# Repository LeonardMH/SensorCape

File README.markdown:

# SensorCape

This is the project repository for the SensorCape for BeagleBone Black. The SensorCape is a highly capable add-on for the BeagleBone that adds the following functionality:

+ 3-axis gyroscope
+ 3-axis accelerometer
+ 3-axis magnetometer (compass)
+ Ambient light sensor
+ Ambient temperature sensor
+ Non-contact temperature sensor
+ Humidity sensor
+ Pressure sensor (Detects altitude changes)
+ 38 kHz IR sensor (Interfaces with common consumer electronics)
+ 4 push-buttons
+ 4 user-configurable LED's 

The repository hosts both the hardware files and the software library that is used to interact with the onboard sensors. Visit the [project page](http://michaelhleonard.com/projects/SensorCape) for further information and documentation.

## Checking out a specific folder

Since 2012 it has been possible to check out a specific folder in a git repository. This means that if you would like to develop or use the software but don't need the hardware files you don't have to clone them to your local computer. See [this stack overflow question](http://stackoverflow.com/questions/600079/is-there-any-way-to-clone-a-git-repositorys-sub-directory-only) for more info or [read this tutorial](http://jasonkarns.com/blog/subdirectory-checkouts-with-git-sparse-checkout/). You may also want to check out [the official documentation](http://schacon.github.io/git/git-read-tree.html#_sparse_checkout).

I would recommend just cloning the entire repository.

# Licenses

Hardware and software are released under the following licenses.

## Hardware

The SensorCape hardware is released under the open source ["SolderPad Hardware License"](http://solderpad.org/licenses/SHL-0.51/). The license disclaimer is below. This is an open source and fairly non-restrictive license.

Copyright SensorCape, Michael Leonard, Copyright and related rights are licensed under the Solderpad Hardware License, Version 0.51 (the “License”); you may not use this file except in compliance with the License. You may obtain a copy of the License at http://solderpad.org/licenses/SHL-0.51. Unless required by applicable law or agreed to in writing, software, hardware and materials distributed under this License is distributed on an “AS IS” BASIS, WITHOUT WARRANTIES OR CONDITIONS OF ANY KIND, either express or implied. See the License for the specific language governing permissions and limitations under the License.

## Software

The software library for the SensorCape (if it is ever finished) is released under the open source ["GNU Lesser General Public License v2.1"](http://www.gnu.org/licenses/lgpl-2.1.html). The license disclaimer is below. This is an open source and fairly non-restrictive license.

SensorCape for BeagleBone Black hardware interface library.
Copyright (C) 2014  Michael Leonard

This library is free software; you can redistribute it and/or
modify it under the terms of the GNU Lesser General Public
License as published by the Free Software Foundation; either
version 2.1 of the License, or any later version.

This library is distributed in the hope that it will be useful,
but WITHOUT ANY WARRANTY; without even the implied warranty of
MERCHANTABILITY or FITNESS FOR A PARTICULAR PURPOSE.  See the GNU
Lesser General Public License for more details.

You should have received a copy of the GNU Lesser General Public
License along with this library; if not, write to the Free Software
Foundation, Inc., 51 Franklin Street, Fifth Floor, Boston, MA  02110-1301  USA

You can contact me on GitHub as user [LeonardMH](http://github.com/LeonardMH).

# Contributors

Michael Leonard - [My Website](http://michaelhleonard.com/)

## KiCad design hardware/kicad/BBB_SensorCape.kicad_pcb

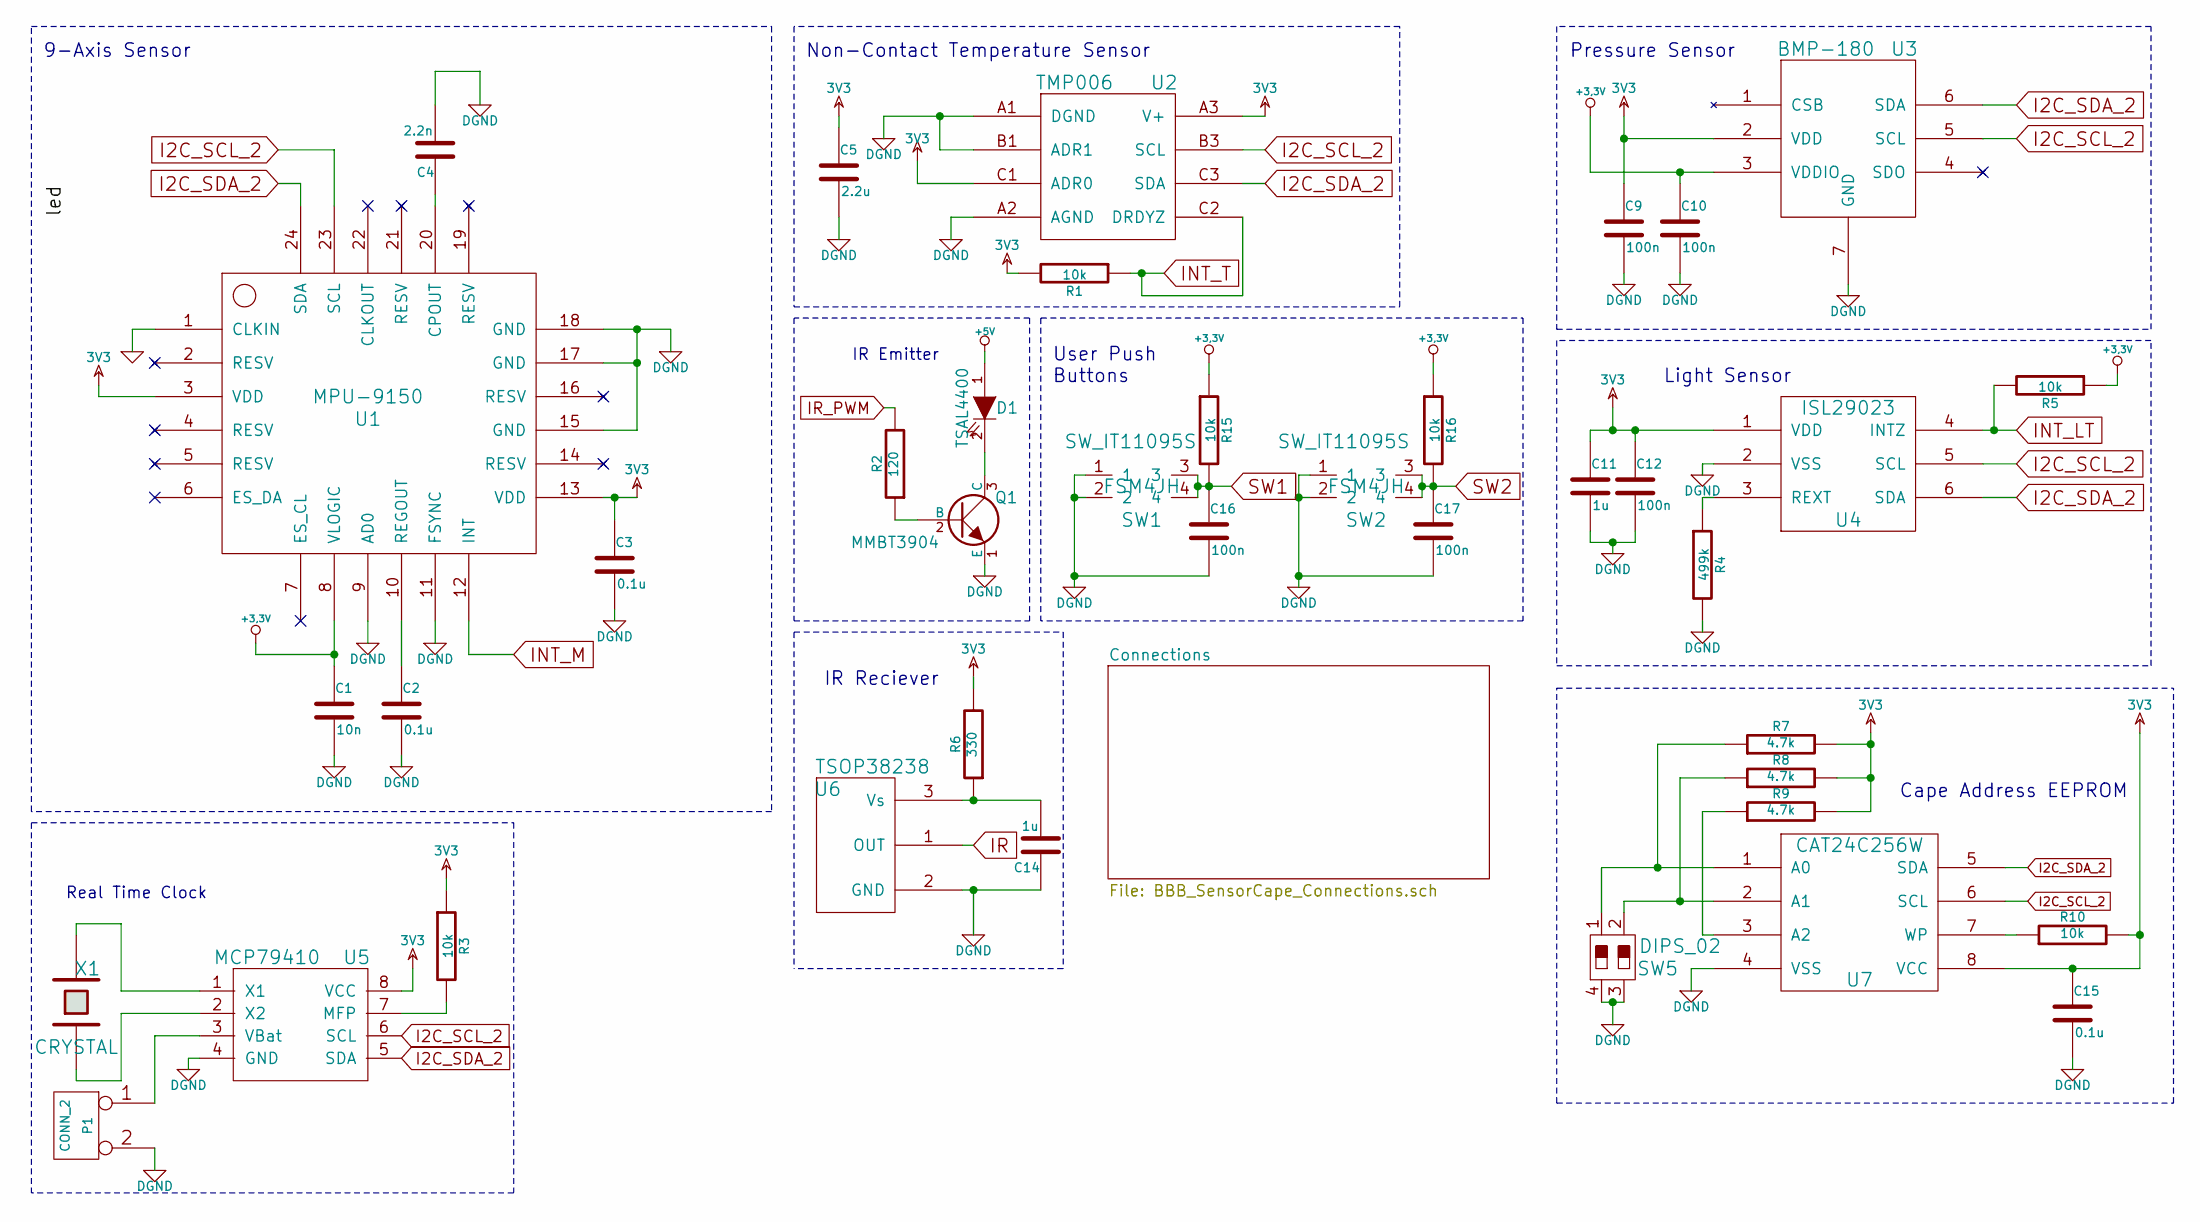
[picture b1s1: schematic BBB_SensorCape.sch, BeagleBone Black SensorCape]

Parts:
C1: 10n
C2, C3, C15: 0.1u
C4: 2.2n
C5: 2.2u
C9, C10, C12, C16, C17: 100n
C11, C14: 1u
D1: TSAL4400
P1: CONN_2
Q1: MMBT3904
R1, R3, R5, R10, R15, R16: 10k
R2: 120
R4: 499k
R6: 330
R7, R8, R9: 4.7k
SW1, SW2: SW_IT11095S; FSM4JH
SW5: DIPS_02
U1: MPU-9150
U2: TMP006
U3: BMP-180
U4: ISL29023
U5: MCP79410
U6: TSOP38238
U7: CAT24C256W
X1: CRYSTAL

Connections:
3V3: C3.1, C5.1, C9.1, C11.1, C12.1, C15.1, R1.2, R3.1, R6.2, R7.2, R8.2, R9.2, R10.2, U1.3 (VDD), U1.13 (VDD), U2.A3 (V+), U2.C1 (ADR0), U3.2 (VDD), U4.1 (VDD), U5.8 (VCC), U7.8 (VCC); also elsewhere on the board
+3.3V: C1.1, C10.1, R5.1, R15.1, R16.1, U1.8 (VLOGIC), U3.3 (VDDIO); also elsewhere on the board
+5V: D1.1 (A); also elsewhere on the board
DGND: C1.2, C2.2, C3.2, C4.2, C5.2, C9.2, C10.2, C11.2, C12.2, C14.1, C15.2, C16.2, C17.2, P1.2 (PM), Q1.1 (E), R4.2, SW1.1, SW1.2, SW2.1, SW2.2, SW5.3, SW5.4, U1.9 (AD0), U1.11 (FSYNC), U1.15 (GND), U1.17 (GND), U1.18 (GND), U2.A1 (DGND), U2.A2 (AGND), U2.B1 (ADR1), U3.7 (GND), U4.2 (VSS), U5.4 (GND), U6.2 (GND), U7.4 (VSS); also elsewhere on the board
I2C_SCL_2: U1.23 (SCL), U2.B3 (SCL), U3.5 (SCL), U4.5 (SCL), U5.6 (SCL), U7.6 (SCL); also elsewhere on the board
I2C_SDA_2: U1.24 (SDA), U2.C3 (SDA), U3.6 (SDA), U4.6 (SDA), U5.5 (SDA), U7.5 (SDA); also elsewhere on the board
INT_LT: R5.2, U4.4 (INTZ); also elsewhere on the board
INT_M: U1.12 (INT); also elsewhere on the board
INT_T: R1.1, U2.C2 (DRDYZ); also elsewhere on the board
IR: U6.1 (OUT); also elsewhere on the board
IR_PWM: R2.2; also elsewhere on the board
unnamed: R9.1, U7.3 (A2)
unnamed: Q1.2 (B), R2.1
unnamed: R10.1, U7.7 (WP)
unnamed: U5.1 (X1), X1.2
unnamed: U5.2 (X2), X1.1
unnamed: P1.1, U5.3 (VBat)
unnamed: D1.2 (K), Q1.3 (C)
unnamed: R3.2, U5.7 (MFP)
unnamed: R4.1, U4.3 (REXT)
unnamed: C4.1, U1.20 (CPOUT)
unnamed: C2.1, U1.10 (REGOUT)
unnamed: R8.1, SW5.2, U7.2 (A1)
unnamed: R7.1, SW5.1, U7.1 (A0)
unnamed: C14.2, R6.1, U6.3 (Vs)
SW1: C16.1, R15.2, SW1.3, SW1.4; also elsewhere on the board
SW2: C17.1, R16.2, SW2.3, SW2.4; also elsewhere on the board

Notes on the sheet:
9-Axis Sensor
Non-Contact Temperature Sensor
Pressure Sensor
Light Sensor
IR Reciever
Cape Address EEPROM
User Push Buttons
IR Emitter
Real Time Clock

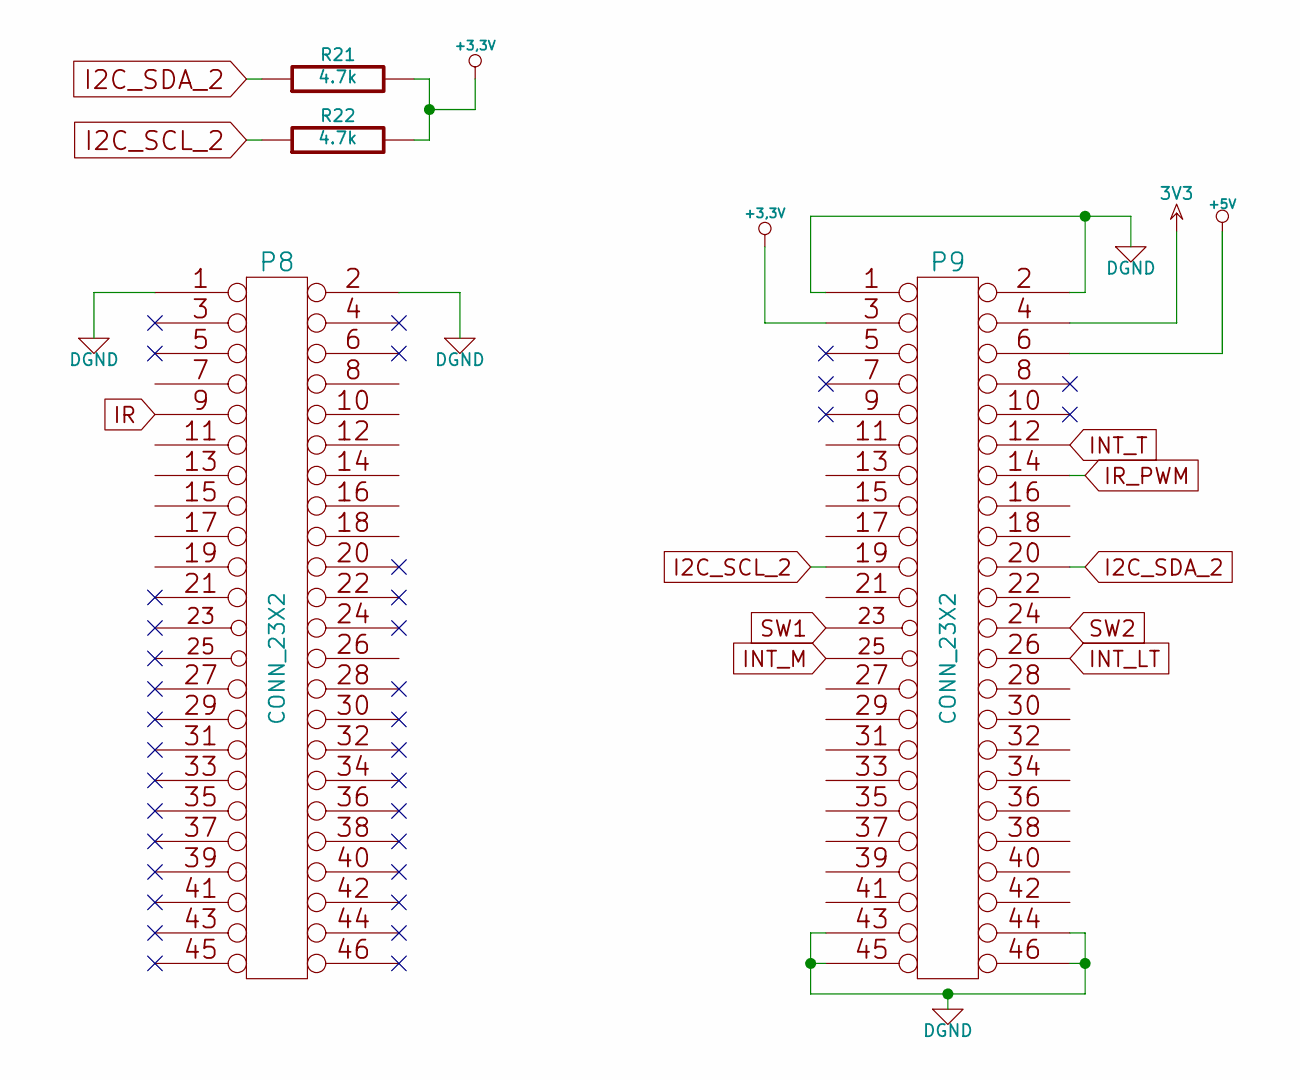
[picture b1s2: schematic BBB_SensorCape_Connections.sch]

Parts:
P8, P9: CONN_23X2
R21, R22: 4.7k

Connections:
3V3: P9.4; also elsewhere on the board
+3.3V: P9.3, R21.2, R22.2; also elsewhere on the board
+5V: P9.6; also elsewhere on the board
DGND: P8.1, P8.2, P9.1, P9.2, P9.43, P9.44, P9.45, P9.46; also elsewhere on the board
I2C_SCL_2: P9.19, R22.1; also elsewhere on the board
I2C_SDA_2: P9.20, R21.1; also elsewhere on the board
INT_LT: P9.26; also elsewhere on the board
INT_M: P9.25; also elsewhere on the board
INT_T: P9.12; also elsewhere on the board
IR: P8.9; also elsewhere on the board
IR_PWM: P9.14; also elsewhere on the board
SW1: P9.23; also elsewhere on the board
SW2: P9.24; also elsewhere on the board

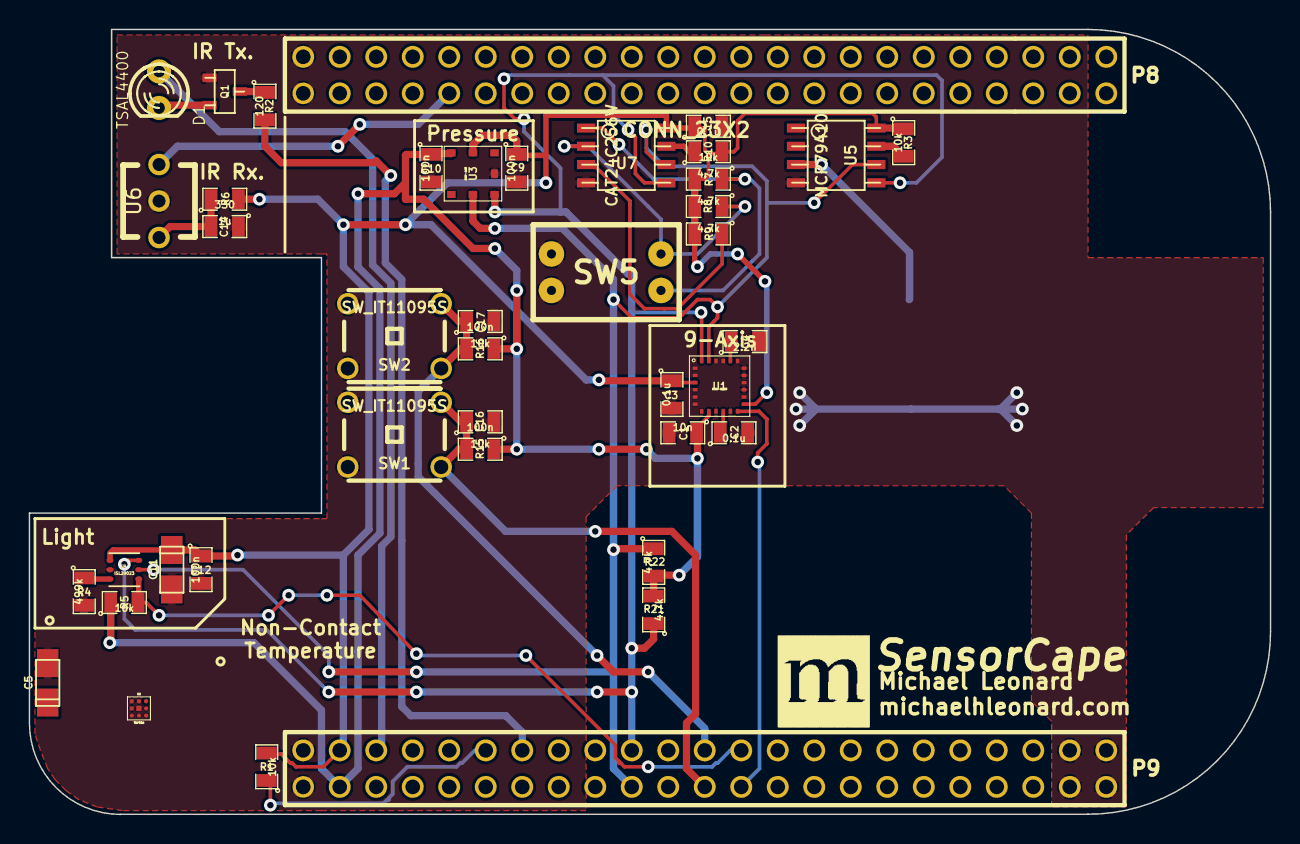
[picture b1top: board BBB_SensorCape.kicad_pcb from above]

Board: 2 copper layers, 86.4 x 54.6 mm, 43 parts (1 on the bottom side), 25 nets.

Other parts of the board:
LOGO: LOGO

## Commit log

2013-07-01 Added a .gitignore
2013-07-02 Initial commit for the library files
2013-07-02 Add Eclipse project files
2013-07-02 Update README.md with directory structure information and a contributor section.
2013-07-02 Updated README again, minor changes
2013-07-02 Updated directory structure. The updated the README to reflect these changes.
2013-07-02 Fixed typos in README and added some better formatting.
2013-07-02 Add some class functionality to SensorCape.h. Began work on motion.h
2013-07-02 Filling in class templates
2013-07-02 Correct makefile
2013-07-02 Trying to synchronize
2013-07-03 Basic LED functionality implemented. Will add GPIO next.
2013-07-03 Added a neat LED test using the USR leds on the BBB.
2013-07-03 Minor updates to SensorCape and motion classes.
2013-07-03 Updated .gitignore
2013-07-03 Updated README.md
    Uses hyperlinks, placed the project page more prominently, added a short description of the SensorCape
2013-07-09 Removed threading from test.cpp
2013-07-09 Begin work on I2C class
2013-07-09 Removed nonessential files from git
2013-07-11 Add basic byte/word read and write functionality to i2c library
2013-07-11 Implemented the functions to read sensor data from MotionSensor, untested
2013-07-11 Added skeleton for testing MotionSensor
2013-07-12 Add readLightData();
2013-07-12 Edited motion library to return correct sized numbers
2013-07-12 Add MotionSensor tests
2014-03-06 Renamed README file
2014-03-06 Renamed SensorCape_v0.2_clib to just clib, I will let git handle version changes
2014-03-06 Updated README and reactivated project
2014-03-06 Added the pylib directory.
2014-03-06 Added hardware files to repository
2014-03-06 Added datasheets
2014-03-06 Added a raw BOM file
2014-03-06 Updated README to discuss new project structure.
2014-03-10 Reworking directory structure, allow git to handle versions
2014-03-10 Added files for hardware version 0.9
2014-03-10 Added files for hardware version 1.0
2014-03-10 Added board and schematic images for v1.0
2014-03-10 Added some automatically generated backup files
2014-03-10 Rasterized the vector images
2014-03-10 Fixed typos and added images to README
2014-04-01 Backing up files
2014-08-01 Restart point
2014-09-11 Update README to include open source licenses for hardware and software.
    Hardware: SolderPad Hardware License
    Software GNU Lesser General Public License v2.1
